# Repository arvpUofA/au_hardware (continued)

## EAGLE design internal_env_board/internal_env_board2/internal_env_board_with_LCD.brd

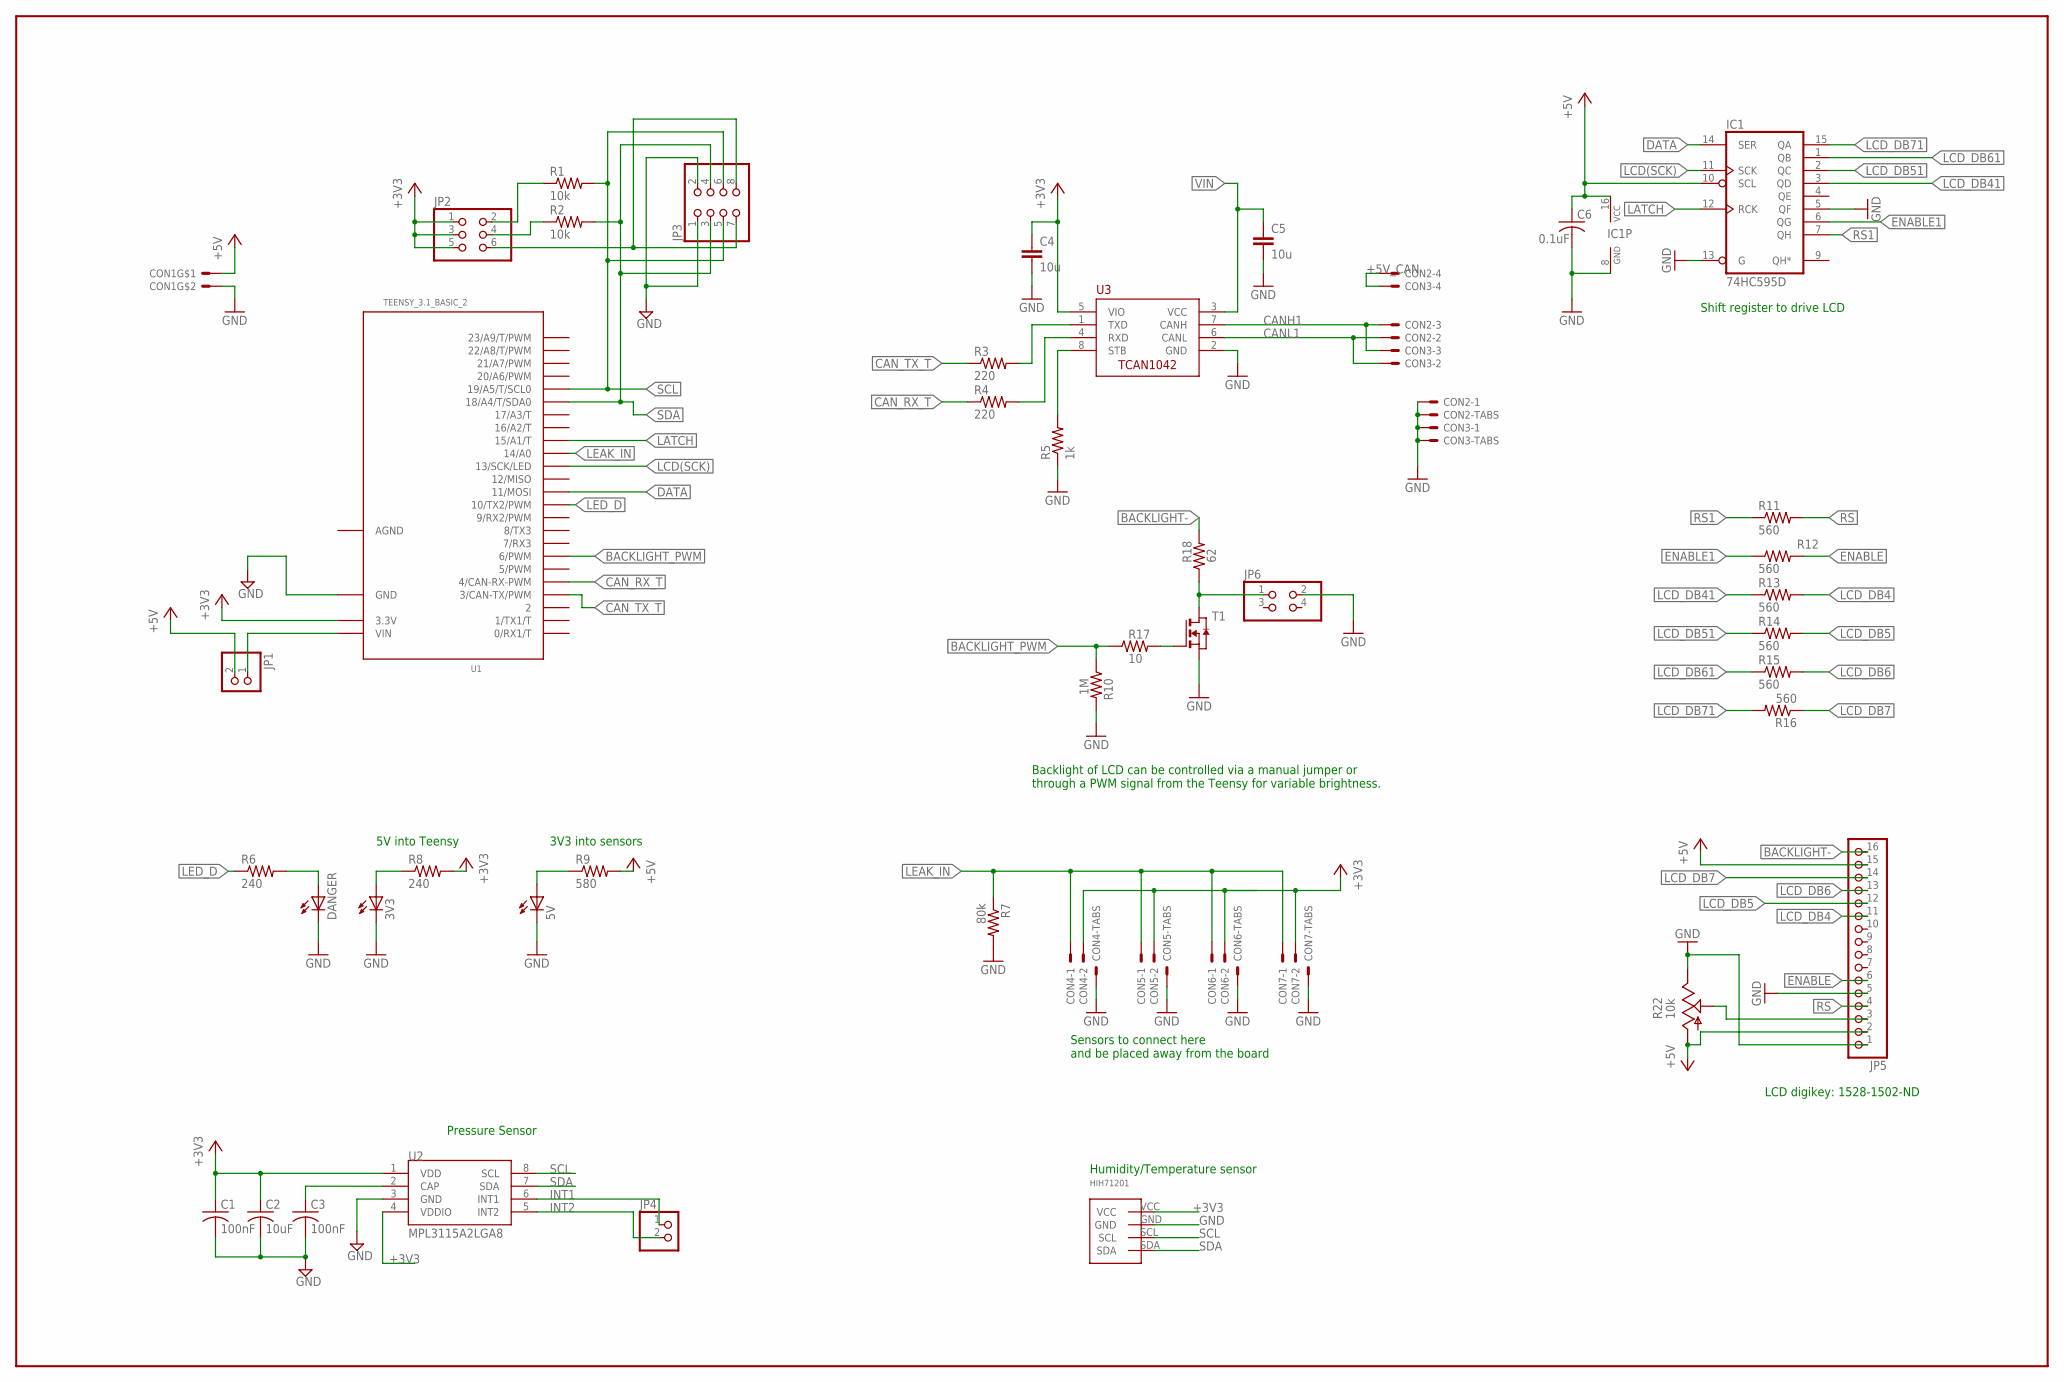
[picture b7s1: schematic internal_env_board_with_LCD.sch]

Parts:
3V3, 5V: LEDSMT1206; 1206
C1, C3: 100nF; C1206
C2: 10uF; C1206
C4, C5: 10u; C0805
C6: 0.1uF; C2012
CON1: MOLEX_5566-2; 5566-2
CON2, CON3: SM04B-GHS-TB
CON4, CON5, CON6, CON7: SM02B-GHS-TB
DANGER: LEDSMT1206; 1206
HIH71201: HIH7120; SIP4
IC1: 74HC595D; SO16
JP1, JP4: PINHD-1X2; 1X02
JP2: PINHD-2X3; 2X03
JP3: PINHD-2X4; 2X04
JP5: PINHD-1X16; 1X16
JP6: PINHD-2X2; 2X02
R1, R2: 10k; R1206
R3, R4: 220; R0805
R5: 1k; R0805
R6, R8: 240; R1206
R7: 80k; R1206
R9: 580; R1206
R10: 1M; R0805
R11, R12, R13, R14, R15, R16: 560; M2012
R17: 10; R0805
R18: 62; R0805
R22: 10k; SM-42/43W
T1: NMOSSOT23; SOT-23
U1: TEENSY_3.1_BASIC_2
U2: MPL3115A2LGA8; LGA8
U3: TCAN1042HVDR; SO-8

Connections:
+3V3: C1.1, C2.1, C4.1, CON4.P$2, CON5.P$2, CON6.P$2, CON7.P$2, HIH71201.VCC, JP2.1, JP2.3, JP2.5, R8.2, U1.3.3V, U2.1 (VDD), U2.4 (VDDIO), U3.5 (VIO)
+5V: C6.1, CON1.1, IC1.10 (SCL), IC1.16 (VCC), JP1.2, JP5.2, JP5.15, R9.2, R22.1 (A)
+5V_CAN: CON2.P$4, CON3.P$4
AGND: U1.AGND
BACKLIGHT-: JP5.16, R18.2
BACKLIGHT_PWM: R10.1, R17.1, U1.6 (6/PWM)
CANH1: CON2.P$3, CON3.P$3, U3.7 (CANH)
CANL1: CON2.P$2, CON3.P$2, U3.6 (CANL)
CAN_RX1: R4.2, U3.4 (RXD)
CAN_RX_T: R4.1, U1.4 (4/CAN-RX-PWM)
CAN_TX2: R3.2, U3.1 (TXD)
CAN_TX_T: R3.1, U1.3 (3/CAN-TX/PWM)
CAP: C3.1, U2.2 (CAP)
DATA: IC1.14 (SER), U1.11 (11/MOSI)
ENABLE: JP5.6, R12.2
ENABLE1: IC1.6 (QG), R12.1
GND: 3V3.C, 5V.C, C1.2, C2.2, C3.2, C4.2, C5.2, C6.2, CON1.2, CON2.P$1, CON2.P$5, CON2.P$6, CON3.P$1, CON3.P$5, CON3.P$6, CON4.P$3, CON4.P$4, CON5.P$3, CON5.P$4, CON6.P$3, CON6.P$4, CON7.P$3, CON7.P$4, DANGER.C, HIH71201.GND, IC1.5 (QF), IC1.8 (GND), IC1.13 (G), JP3.1, JP3.2, JP5.1, JP5.5, JP6.2, R5.1, R7.2, R10.2, R22.3 (E), T1.2 (S), U1.GND, U2.3 (GND), U3.2 (GND)
I2C_3V1: JP2.6, JP3.7, JP3.8
INT1: JP4.1, U2.6 (INT1)
INT2: JP4.2, U2.5 (INT2)
LATCH: IC1.12 (RCK), U1.15/A1 (15/A1/T)
LCD(SCK): IC1.11 (SCK), U1.13 (13/SCK/LED)
LCD_DB4: JP5.11, R13.2
LCD_DB5: JP5.12, R14.2
LCD_DB6: JP5.13, R15.2
LCD_DB7: JP5.14, R16.1
LCD_DB41: IC1.3 (QD), R13.1
LCD_DB51: IC1.2 (QC), R14.1
LCD_DB61: IC1.1 (QB), R15.1
LCD_DB71: IC1.15 (QA), R16.2
LEAK_IN: CON4.P$1, CON5.P$1, CON6.P$1, CON7.P$1, R7.1, U1.14/A0
LED_D: R6.1, U1.10 (10/TX2/PWM)
unnamed: DANGER.A, R6.2
unnamed: 5V.A, R9.1
unnamed: R17.2, T1.3 (G)
unnamed: JP6.1, R18.1, T1.1 (D)
unnamed: 3V3.A, R8.1
unnamed: JP5.3, R22.2 (S)
RS: JP5.4, R11.2
RS1: IC1.7 (QH), R11.1
SCL: HIH71201.SCL, JP3.5, JP3.6, R1.2, U1.19/A5 (19/A5/T/SCL0), U2.8 (SCL)
SCL_3V1: JP2.2, R1.1
SDA: HIH71201.SDA, JP3.3, JP3.4, R2.2, U1.18/A4 (18/A4/T/SDA0), U2.7 (SDA)
SDA_3V1: JP2.4, R2.1
STB1: R5.2, U3.8 (STB)
VIN: C5.1, JP1.1, U1.VIN, U3.3 (VCC)

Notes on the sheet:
Pressure Sensor
5V into Teensy
3V3 into sensors
Humidity/Temperature sensor
Sensors to connect here and be placed away from the board
LCD digikey: 1528-1502-ND
Shift register to drive LCD
Backlight of LCD can be controlled via a manual jumper or through a PWM signal from the Teensy for variable brightness.

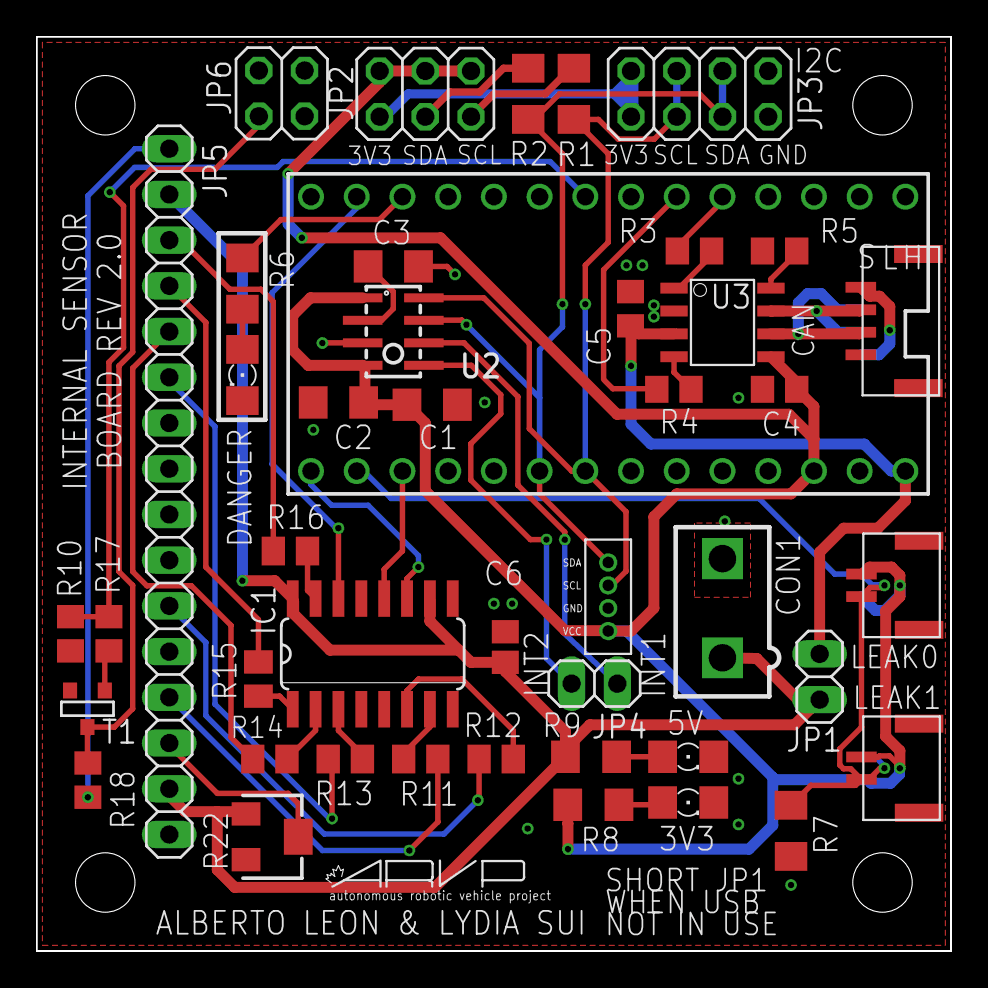
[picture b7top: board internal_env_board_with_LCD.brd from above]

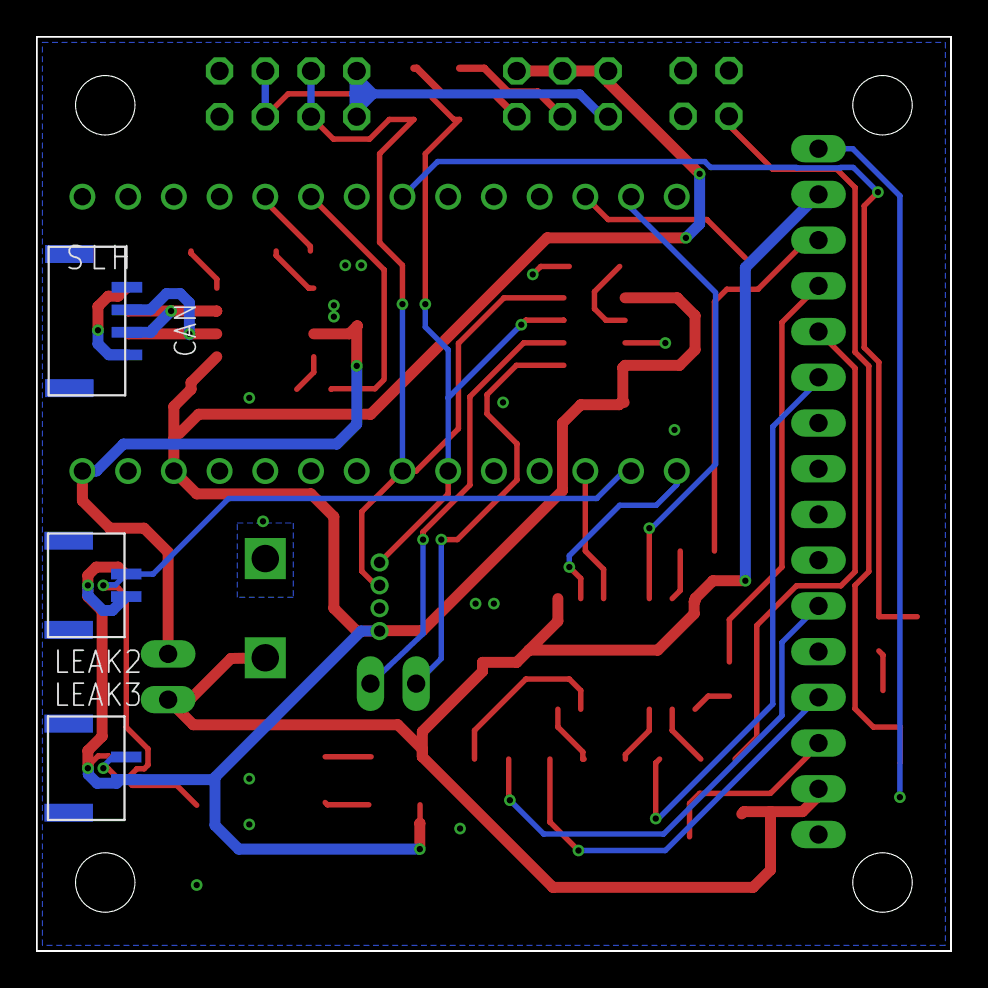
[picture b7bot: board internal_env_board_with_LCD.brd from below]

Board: 2 copper layers, 50.8 x 50.8 mm, 53 parts (3 on the bottom side), 45 nets.

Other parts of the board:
U$1: LOGO2
U$4: A5L-LOC
U$5, U$6, U$7, U$8: STAND-OFF

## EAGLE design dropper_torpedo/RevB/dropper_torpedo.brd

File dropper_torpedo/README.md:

<p>This is the dropper torpedo board schematic</p>
<p>Board layout will be added soon</p>

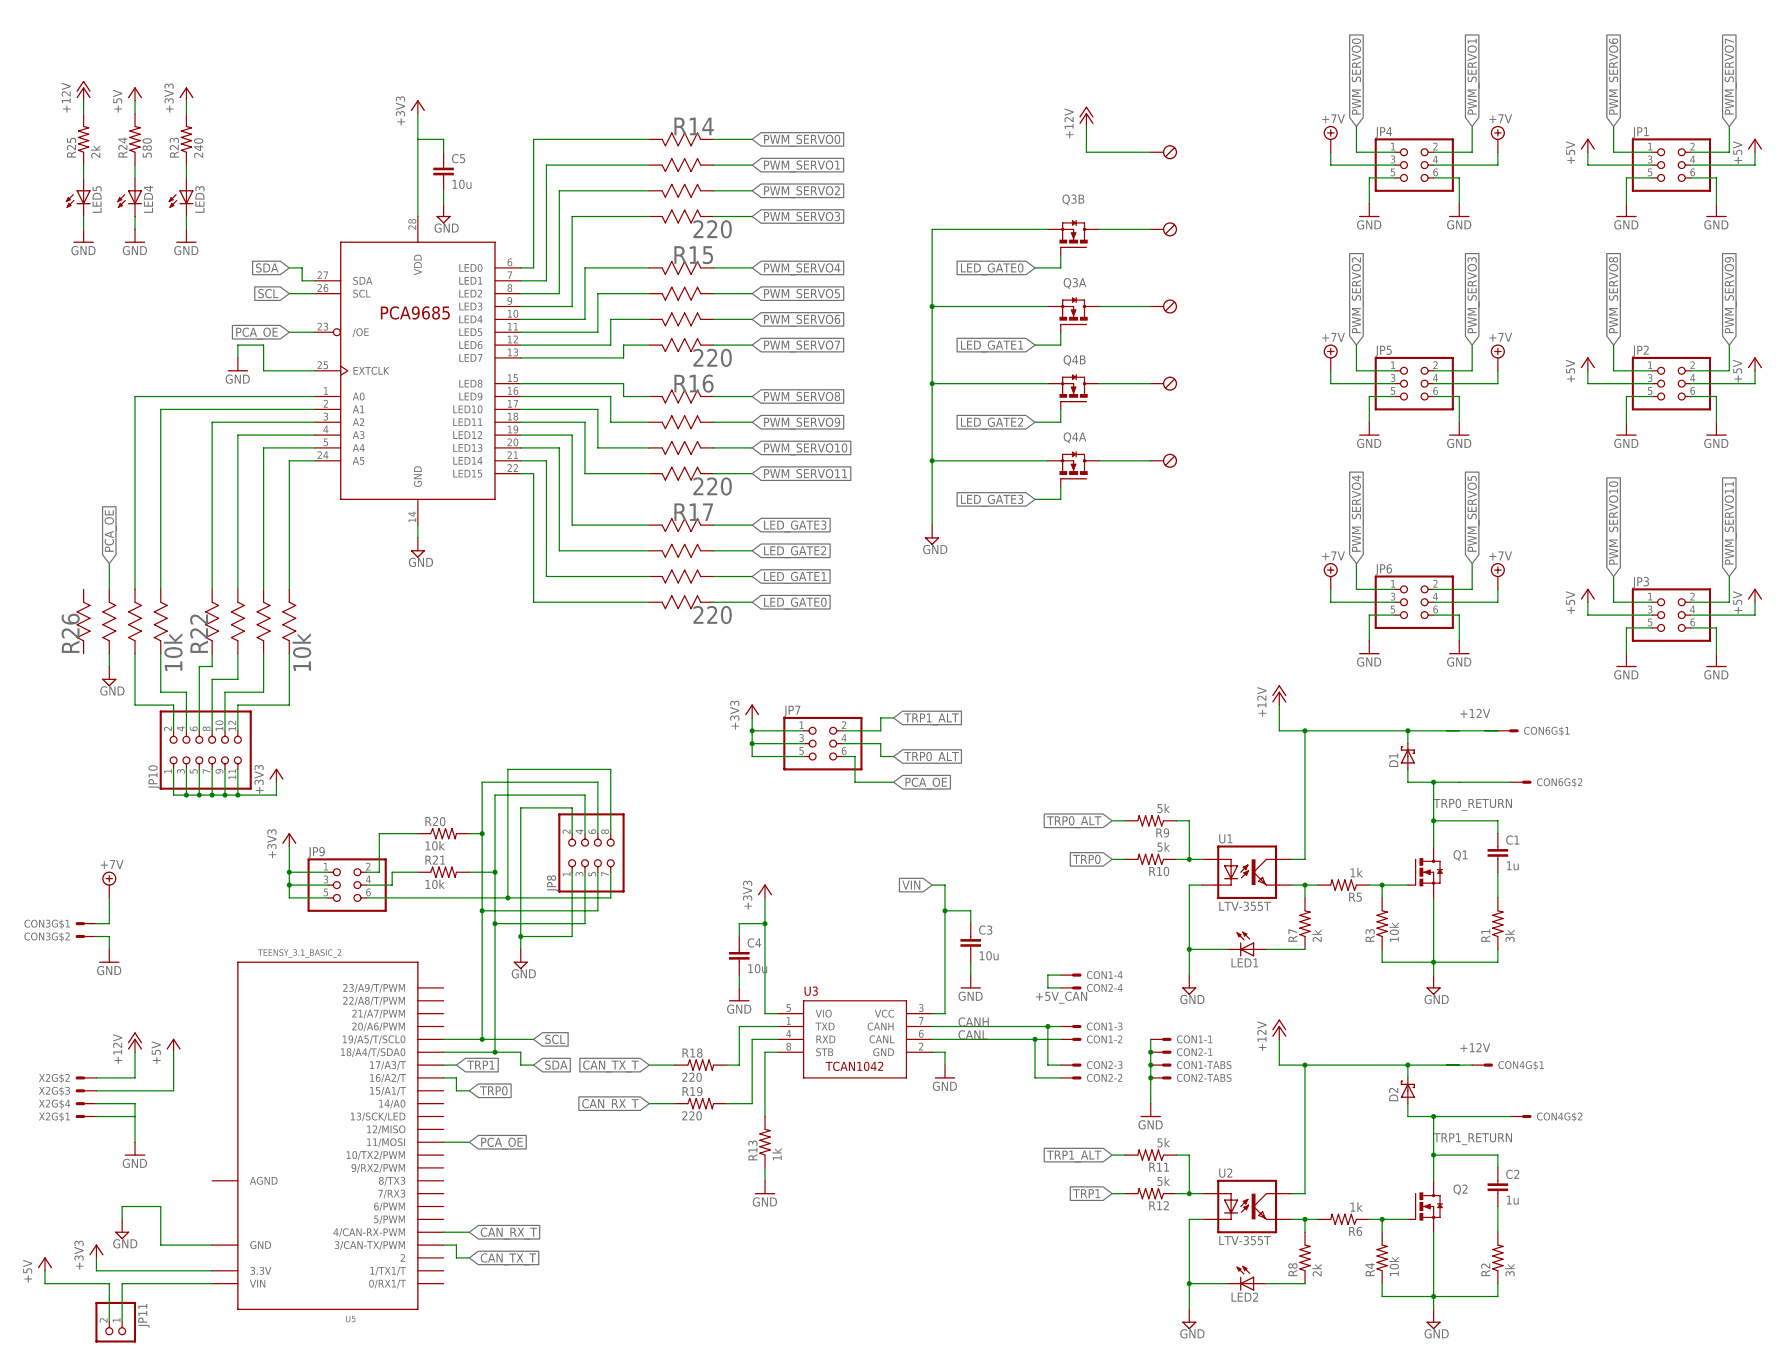
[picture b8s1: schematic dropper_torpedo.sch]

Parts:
C1, C2: 1u; C1206
C3, C4, C5: 10u; C0805
CON1, CON2: SM04B-GHS-TB
CON3, CON4, CON6: MOLEX_5566-2; 5566-2
D1, D2: STPS1L30A; DO214AC
JP1, JP2, JP3, JP4, JP5, JP6, JP7, JP9: PINHD-2X3; 2X03
JP8: PINHD-2X4; 2X04
JP10: PINHD-2X6; 2X06
JP11: PINHD-1X2; 1X02
LED1, LED2, LED3, LED4, LED5: LEDCHIPLED_1206; CHIPLED_1206
Q1, Q2: SI4896DY-T1-E3; SO-8
Q3, Q4: IRL6372TRPBF; SO-8
R1, R2: 3k; R1206
R3, R4, R20, R21: 10k; R1206
R5, R6: 1k; R1206
R7, R8, R25: 2k; R1206
R9, R10, R11, R12: 5k; R0805
R13: 1k; R0805
R14, R15, R16, R17: 220; EXBV8V-M
R18, R19: 220; R0805
R22, R26: 10k; EXBV8V-M
R23: 240; R1206
R24: 580; R1206
U1, U2: LTV-355T; SMD4
U3: TCAN1042HVDR; SO-8
U4: PCA9685PW; TSSOP28
U5: TEENSY_3.1_BASIC_2
X1: OSTVN05A150
X2: MOLEX_5566-4; 5566-4

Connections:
+3V3: C4.1, C5.1, JP7.1, JP7.3, JP7.5, JP9.1, JP9.3, JP9.5, JP10.1, JP10.3, JP10.5, JP10.7, JP10.9, JP10.11, R23.2, U3.5 (VIO), U4.28 (VDD), U5.3.3V
+5V: JP1.3, JP1.4, JP2.3, JP2.4, JP3.3, JP3.4, JP11.2, R24.2, X2.3
+5V_CAN: CON1.P$4, CON2.P$4
+7V: CON3.1, JP4.3, JP4.4, JP5.3, JP5.4, JP6.3, JP6.4
+12V: CON4.1, CON6.1, D1.C, D2.C, R25.2, U1.COLLECTOR (COL), U2.COLLECTOR (COL), X1.P$5, X2.2
A0: R26.6 (66), U4.1 (A0)
A0+: JP10.2, R26.3 (35)
A1: R26.5 (58), U4.2 (A1)
A1+: JP10.4, R26.4 (47)
A2: R22.8 (82), U4.3 (A2)
A2+: JP10.6, R22.1 (11)
A3: R22.7 (74), U4.4 (A3)
A3+: JP10.8, R22.2 (23)
A4: R22.6 (66), U4.5 (A4)
A4+: JP10.10, R22.3 (35)
A5: R22.5 (58), U4.24 (A5)
A5+: JP10.12, R22.4 (47)
AGND: U5.AGND
CANH: CON1.P$3, CON2.P$3, U3.7 (CANH)
CANL: CON1.P$2, CON2.P$2, U3.6 (CANL)
CAN_RX: R19.2, U3.4 (RXD)
CAN_RX_T: R19.1, U5.4 (4/CAN-RX-PWM)
CAN_TX1: R18.2, U3.1 (TXD)
CAN_TX_T: R18.1, U5.3 (3/CAN-TX/PWM)
GND: C3.2, C4.2, C5.2, CON1.P$1, CON1.P$5, CON1.P$6, CON2.P$1, CON2.P$5, CON2.P$6, CON3.2, JP1.5, JP1.6, JP2.5, JP2.6, JP3.5, JP3.6, JP4.5, JP4.6, JP5.5, JP5.6, JP6.5, JP6.6, JP8.1, JP8.2, LED1.C, LED2.C, LED3.C, LED4.C, LED5.C, Q1.1 (S), Q1.2 (S), Q1.3 (S), Q2.1 (S), Q2.2 (S), Q2.3 (S), Q3.1 (S), Q3.3 (S), Q4.1 (S), Q4.3 (S), R1.1, R2.1, R3.1, R4.1, R13.1, R26.2 (23), U1.CATHODE (C), U2.CATHODE (C), U3.2 (GND), U4.14 (GND), U4.25 (EXTCLK), U5.GND, X2.1, X2.4
I2C_3V3: JP8.7, JP8.8, JP9.6
LED_DRAIN0: Q3.7 (D), Q3.8 (D), X1.P$4
LED_DRAIN1: Q3.5 (D), Q3.6 (D), X1.P$3
LED_DRAIN2: Q4.7 (D), Q4.8 (D), X1.P$2
LED_DRAIN3: Q4.5 (D), Q4.6 (D), X1.P$1
LED_GATE0: Q3.2 (G), R17.4 (47)
LED_GATE1: Q3.4 (G), R17.3 (35)
LED_GATE2: Q4.2 (G), R17.2 (23)
LED_GATE3: Q4.4 (G), R17.1 (11)
unnamed: LED1.A, R7.1
unnamed: LED2.A, R8.1
unnamed: LED3.A, R23.1
unnamed: LED4.A, R24.1
unnamed: LED5.A, R25.1
PCA_OE: JP7.6, R26.7 (74), U4.23 (/OE), U5.11 (11/MOSI)
PWM_CH0: R14.8 (82), U4.6 (LED0)
PWM_CH1: R14.7 (74), U4.7 (LED1)
PWM_CH2: R14.6 (66), U4.8 (LED2)
PWM_CH3: R14.5 (58), U4.9 (LED3)
PWM_CH4: R15.8 (82), U4.10 (LED4)
PWM_CH5: R15.7 (74), U4.11 (LED5)
PWM_CH6: R15.6 (66), U4.12 (LED6)
PWM_CH7: R15.5 (58), U4.13 (LED7)
PWM_CH8: R16.8 (82), U4.15 (LED8)
PWM_CH9: R16.7 (74), U4.16 (LED9)
PWM_CH10: R16.6 (66), U4.17 (LED10)
PWM_CH11: R16.5 (58), U4.18 (LED11)
PWM_CH12: R17.8 (82), U4.19 (LED12)
PWM_CH13: R17.7 (74), U4.20 (LED13)
PWM_CH14: R17.6 (66), U4.21 (LED14)
PWM_CH15: R17.5 (58), U4.22 (LED15)
PWM_SERVO0: JP4.1, R14.1 (11)
PWM_SERVO1: JP4.2, R14.2 (23)
PWM_SERVO2: JP5.1, R14.3 (35)
PWM_SERVO3: JP5.2, R14.4 (47)
PWM_SERVO4: JP6.1, R15.1 (11)
PWM_SERVO5: JP6.2, R15.2 (23)
PWM_SERVO6: JP1.1, R15.3 (35)
PWM_SERVO7: JP1.2, R15.4 (47)
PWM_SERVO8: JP2.1, R16.1 (11)
PWM_SERVO9: JP2.2, R16.2 (23)
PWM_SERVO10: JP3.1, R16.3 (35)
PWM_SERVO11: JP3.2, R16.4 (47)
RC0: C1.2, R1.2
RC1: C2.2, R2.2
SCL: JP8.5, JP8.6, R20.2, U4.26 (SCL), U5.19/A5 (19/A5/T/SCL0)
SCL_3V3: JP9.2, R20.1
SDA: JP8.3, JP8.4, R21.2, U4.27 (SDA), U5.18/A4 (18/A4/T/SDA0)
SDA_3V3: JP9.4, R21.1
STB: R13.2, U3.8 (STB)
TOPTO_A0: R9.1, R10.1, U1.ANODE (A)
TOPTO_A1: R11.1, R12.1, U2.ANODE (A)
TOPTO_E0: R5.2, R7.2, U1.EMITTER (EMIT)
TOPTO_E1: R6.2, R8.2, U2.EMITTER (EMIT)
TRP0: R10.2, U5.16/A2 (16/A2/T)
TRP0_ALT: JP7.4, R9.2
TRP0_RETURN: CON6.2
TRP1: R12.2, U5.17/A3 (17/A3/T)
TRP1_ALT: JP7.2, R11.2
TRP1_RETURN: C2.1, CON4.2, D2.A, Q2.5 (D), Q2.6 (D), Q2.7 (D), Q2.8 (D)
TRP_GATE0: Q1.4 (G), R3.2, R5.1
TRP_GATE1: Q2.4 (G), R4.2, R6.1
TRP_RETURN0: C1.1, D1.A, Q1.5 (D), Q1.6 (D), Q1.7 (D), Q1.8 (D)
VIN: C3.1, JP11.1, U3.3 (VCC), U5.VIN

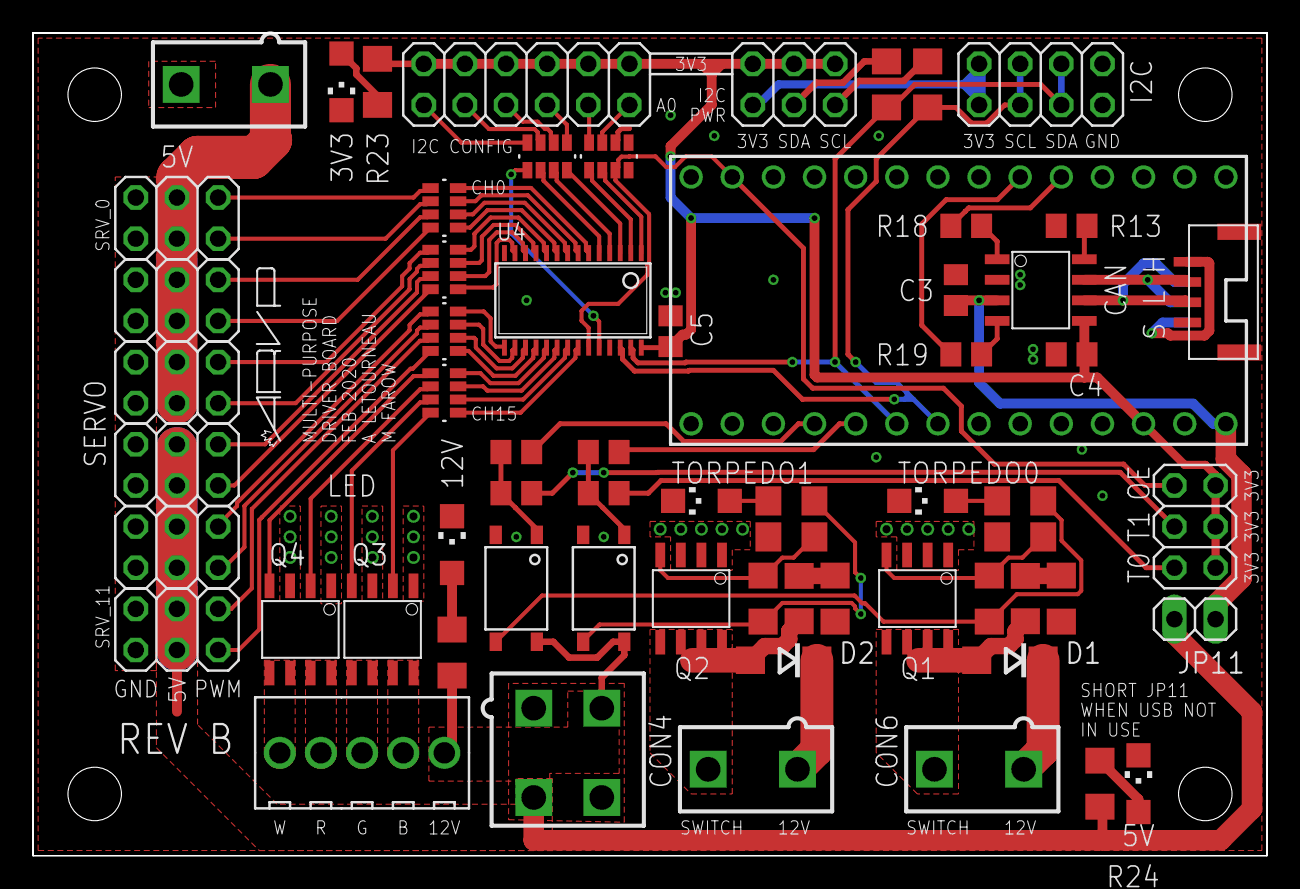
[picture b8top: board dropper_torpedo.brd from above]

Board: 2 copper layers, 76.2 x 50.8 mm, 72 parts (1 on the bottom side), 87 nets.

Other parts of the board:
U$5: LOGO3
U$6: LETTER_L
U$7: DOCFIELD
U$8, U$9, U$10, U$11: STAND-OFF

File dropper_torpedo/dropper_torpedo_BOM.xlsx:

Torpedo Board V3: Bill of Materials
Shematic Reference Number | Part Description | Manufacturer Part Number | Datasheet | Price | Quantity | Total Cost | Customer Reference
Q1, Q2 | MOSFET N-CH 80V 6.7A 8-SOIC | SI4896DY-T1-E3 | http://www.vishay.com/docs/71300/71300.pdf | 2.37 | 2 | 4.74 | DROP_TORP
Q3, Q4 | MOSFET 2N-CH 30V 8.1A 8SOIC | IRL6372TRPBF | http://www.infineon.com/dgdl/irl6372pbf.pdf?fileId=5546d4625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 | 1.15 | 2 | 2.3 | DROP_TORP
D1, D2 | DIODE SCHOTTKY 30V 1A SMA | STPS1L30A | http://www.st.com/content/ccc/resource/technical/document/da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 | 0.53 | 2 | 1.06 | DROP_TORP
U1, U2 | OPTOISO 3.75KV DARLINGTON 4SOP | LTV-355T | http://optoelectronics.liteon.com/upload/download/DS70-2001-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 | 0.74 | 2 | 1.48 | DROP_TORP
TRM1, TRM2 | TERM BLOCK 5.08MM HORZ 2POS PCB | OSTTC022162 | http://www.on-shore.com/wp-content/uploads/2015/09/osttcxx2162.pdf | 1.08 | 2 | 2.16 | DROP_TORP
LED1-5 | LED GREEN CLEAR 1206 SMD | LTST-C150GKT | http://optoelectronics.liteon.com/upload/download/DS-22-98-0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 | 0.46 | 2 | 0.92 | DROP_TORP
X2 | CONN HEADER 4POS 4.2MM VERT TIN | 39281043 | http://www.molex.com/pdm_docs/sd/039281043_sd.pdf | 1.04 | 1 | 1.04 | DROP_TORP
R14-17 | RES ARRAY 4 RES 220 OHM 1206 | EXB-V8V221JV | https://media.digikey.com/pdf/Data%20Sheets/Panasonic%20Resi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 | 0.14 | 4 | 0.56 | DROP_TORP
R22,26 | RES ARRAY 4 RES 10K OHM 1206 | EXB-V8V103JV | https://media.digikey.com/pdf/Data%20Sheets/Panasonic%20Resi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 | 0.14 | 2 | 0.28 | DROP_TORP
X1 | CONN TERM BLOCK 2.54MM 5POS PCB | OSTVN05A150 | http://www.on-shore.com/wp-content/uploads/2015/09/ostvnxxa150.pdf | 2.34 | 1 | 2.34 | DROP_TORP
C1,2 | CAP CER 1UF 50V X7R 1206 | CL31B105KBHNNNE | https://www.samsungsem.com/kr/support/product-search/mlcc/__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 | 0.26 | 2 | 0.52 | DROP_TORP
C3,4,5 | CAP CER 10UF 16V X7R 0805 | CL21B106KOQNNNG | http://www.samsungsem.com/kr/support/product-search/mlcc/CL2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 | 0.39 | 3 | 1.17 | DROP_TORP
R23 | RES SMD 240 OHM 1% 1/4W 1206 | RC1206FR-07240RL | http://www.yageo.com/documents/recent/PYu-RC_Group_51_RoHS_L_7.pdf | 0.047 | 1 | 0.047 | DROP_TORP
R24 | RES SMD 576 OHM 1% 1/4W 1206 | RC1206FR-07576RL | http://www.yageo.com/documents/recent/PYu-RC_Group_51_RoHS_L_7.pdf | 0.047 | 1 | 0.047 | DROP_TORP
R5,6 | RES SMD 1K OHM 1% 1/4W 1206 | RC1206FR-071KL | http://www.yageo.com/documents/recent/PYu-RC_Group_51_RoHS_L_7.pdf | 0.047 | 2 | 0.094 | DROP_TORP
R7,8,25 | RES SMD 2K OHM 1% 1/4W 1206 | RC1206FR-072KL | http://www.yageo.com/documents/recent/PYu-RC_Group_51_RoHS_L_7.pdf | 0.047 | 3 | 0.141 | DROP_TORP
R9-12 | RES SMD 4.99K OHM 1% 1/4W 0805 | RC0805FR-074K99L | http://www.yageo.com/documents/recent/PYu-RC_Group_51_RoHS_L_8.pdf | 0.031 | 4 | 0.124 | DROP_TORP
R18, 19 | RES SMD 220 OHM 1% 1/8W 0805 | RC0805FR-07220RL | http://www.yageo.com/documents/recent/PYu-RC_Group_51_RoHS_L_7.pdf | 0.031 | 2 | 0.062 | DROP_TORP
R1,2 | RES SMD 3K OHM 1% 1/4W 1206 | RC1206FR-073KL | http://www.yageo.com/documents/recent/PYu-RC_Group_51_RoHS_L_7.pdf | 0.047 | 2 | 0.094 | DROP_TORP
R3,4,20,21 | RES SMD 10K OHM 1% 1/4W 1206 | RC1206FR-0710KL | http://www.yageo.com/documents/recent/PYu-RC_Group_51_RoHS_L_7.pdf | 0.047 | 4 | 0.188 | DROP_TORP
R13 | RES SMD 1K OHM 1% 1/8W 0805 | RC0805FR-071KL | http://www.yageo.com/documents/recent/PYu-RC_Group_51_RoHS_L_7.pdf | 0.034 | 1 | 0.034 | DROP_TORP
U4 | IC LED DRIVER RGBA 28-TSSOP | PCA9685PW,118 | http://www.nxp.com/documents/data_sheet/PCA9685.pdf | 3.3 | 1 | 3.3 | DROP_TORP
Teensy 3.2 | CONN HEADER FMALE 14POS .1" GOLD | PPPC141LFBN-RC | http://www.sullinscorp.com/drawings/78_P(N)PxCxxxLFBN-RC,_10492-H.pdf | 1.28 | 2 | 2.56 | DROP_TORP
JP1-7,9,10 | DIL VERTICAL PC TAIL PIN HEADER 2x3 | M20-9980345 | https://cdn.harwin.com/pdfs/M20-998.pdf | 0.348 | 9 | 3.132 | DROP_TORP
JP8 | DIL VERTICAL PC TAIL PIN HEADER 2x4 | M20-9980445 | https://cdn.harwin.com/pdfs/M20-998.pdf | 0.48 | 1 | 0.48 | DROP_TORP
JP11 | SIL VERTICAL PC TAIL PIN HEADER 1x2 | M20-9990245 | https://cdn.harwin.com/pdfs/M20-999.pdf | 0.2 | 1 | 0.2 | DROP_TORP
U3 | IC TXRX CAN FAULT PROT 8SOIC | TCAN1042HVDRQ1 | http://www.ti.com/lit/ds/symlink/tcan1042hgv-q1.pdf | 2.05 | 1 | 2.05 | DROP_TORP
CON3 | CONN HEADER 2POS 4.2MM VERT TIN | 39281023 | http://www.molex.com/pdm_docs/sd/039281023_sd.pdf | 0.83 | 1 | 0.83 | DROP_TORP
CON1,2 | CONN HEADER GH SIDE 3POS 1.25MM | SM03B-GHS-TB(LF)(SN) | http://www.jst-mfg.com/product/pdf/eng/eGH.pdf | 0.68 | 2 | 1.36 | DROP_TORP
- | CONN JUMPER SHORTING GOLD FLASH | SPC02SYAN | http://www.sullinscorp.com/drawings/134_C02SYAN_11134.pdf | 0.083 | 9 | 0.747 | DROP_TORP
 |  |  |  |  | Total | 34.06

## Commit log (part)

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2017-11-07 Fixed issue with CAM files
2017-11-11 Schematic
2017-11-13 Schematic with suggestions made by Alain implemented.
    I've implemented the suggestions from the last meeting, and I will begin work on the PCB once it is reviewed.
2017-11-14 not sure how to add the yellow signal lines
2017-11-14 implemented newest design block and rearranged pcb
2017-11-17 Schematic: Update with MOSFET to switch PV_OUT
2017-11-18 2x2 inch board and trace routes
2017-11-20 Updated CAN Design Block To use JST connectors.
2017-11-22 changed dimensions and fixed layer text
2017-11-23 Schematic with name changes on the LEDs
2017-11-24 Schematic: Value of a resistor is changed
2017-11-25 Swapped old MPL3115 footprint with new one
2017-11-25 In BOM, changed .47uF capacitor to one with .55mm thickness
2017-11-25 Schematic: Connected pin 3 on JP2 to VCC
2017-11-25 Board (v.4)
    Fixed the issue of islanding.
2017-11-25 Added jumpers to schematic and finished the PCB. The PCB has not been checked with the new DRC.
2017-11-26 schematic for i2c,uart, LEDs
2017-11-26 Rearranged file structure
2017-11-26 Removed extra folder
2017-11-28 CAM files, Image files
2017-11-29 Fixes as asked for in pull request
2017-11-30 Added jumpers for the shield connection on the JST connectors.
2017-11-30 Added jumpers for CAN enable.
2017-12-01 Added jumpers to I2C
2017-12-01 minor fixes, cant find jst-gh part
2017-12-01 new conn for can bus and leak sensors, new routes
2017-12-02 Added some GND VIAs
2017-12-02 JST connectors, traces
2017-12-02 Spaced out JST connectors
2017-12-02 Completed schematic
2017-12-03 Slightly modified layout+routing
2017-12-03 Routed most components
2017-12-03 Changed folder structure
2017-12-03 Changed layout, routing; Generated CAM files
2017-12-03 Re-added old sch and brd
2017-12-03 Fixed issue where motors could still find ground return path even when battery was disconnected by mosfet
2017-12-03 Added 5V pin to CAN connectors in case ESC CAN transceivers require external 5V
2017-12-03 Increased text size for LEDs
2017-12-04 completed board
2017-12-04 Added BOM and the parts order list
2017-12-05 Added BOM; Changed LED resistor values
2017-12-05 Corrected 2x3 header qty in BOM
2017-12-06 Edited the BOM, cleaned up some errors.
2017-12-07 Fixed qty of 1x2 headers
2017-12-08 Fixed qty JST 2 pin conn
2017-12-08 Made BOM + CAM
2017-12-27 updated sonar part list with available qts
2018-01-14 Added libraries and design block
2018-01-17 Added LDO
2018-01-19 Schematic and board with fuse
2018-01-20 added power and communication wiring diagram. WIP
2018-01-22 Added proper paging and most power diagrams
2018-01-26 Board File Upload
2018-02-03 Final board design with png files for board and schematic
2018-02-04 Added base schematic file
2018-02-04 Added amplifier.dbl
2018-02-04 Added peak_detector.dbl
2018-02-04 Added nxp_60.lbr
2018-02-04 First Revision
    First Revision of the variable gain amplifier for the sonar board. Designed for testing.
2018-02-04 Revert "Merge branch 'amplifier' into sonar_preprocessor_v3"
    This reverts commit 540102cfd5a4b1681464287940d3c6b068a53623, reversing
    changes made to de64d5886ef795e5a61c97630054a831d31d3a9c.
2018-02-05 re-upload after failed merge
2018-02-06 added all components except for connectors and test points
2018-02-07 adjuste filter C parameters
2018-02-07 Using 0.2" pitch headers
2018-02-09 added sugestions from Mike Bardwell to schematic
2018-02-09 *forgot to save on previous commit
2018-02-10 added names to clk/i2c pins
2018-02-11 Completed changes discussed in last design review and ran through DRC
2018-02-11 Renamed files
2018-02-11 Modified silk screen
2018-02-12 Pushed BOM file
2018-02-12 Changed layer of dimensions; Added CAM files
2018-02-13 Complted bom, made a couple package changes on schematic to conver them to 0805
2018-02-19 Created initial peak detector design block
2018-03-10 Made some changes recommended by Alain, still need to do more
2018-03-10 Finished implementing Alain's recommendations
2018-03-10 Added BeagleBone custom cape lbr
2018-03-10 Replaced beaglebone footprint with some pinheaders
2018-03-12 Work on headers
2018-03-17 Final commit for peak detector, 100% verified working.
2018-03-21 Reworked board dimensions and mounting
2018-03-24 added filter design block
2018-03-24 5, 3.3, and -5V design
2018-03-29 Added the design block
    All components on the top layer. Made footprint as small as possible.
    Area is less than 15.30 x 10.9 mm
2018-03-30 Cheaper Options
2018-03-30 Added a little bit more clearance
2018-03-31 placed bypass caps and Rclk on bottom of board. Renamed BOM.xlsx to BOM_prototype.xlsx
2018-03-31 LT1117 and LT1962 schematics, PCBs, and design blocks
2018-03-31 added polarity indicator to Clock Generator
2018-04-04 More layout work
2018-04-04 Rearranged files
2018-04-05 Placed power supply, peak detector, filter
2018-04-13 reworked filter and clock routing
2018-04-13 Added clock output. minor clock routing changes
2018-04-14 some more work
2018-04-15 Started BOM
2018-04-20 Completed BOM; Routed peak detector BJT base
2018-05-10 First draft of the schematic and PCB
2018-05-10 deleted older versions
2018-05-12 Changed routings
2018-05-26 Removed extra GND pads, increased drill size to 1.5mm'
2018-05-26 Added mountable buffer board
2018-05-26 Modified layout
2018-05-27 Implemented Mikes suggestions
2018-05-27 Added CAM files; Changed power trace layout; Renamed test pads
2018-05-28 Changed VS routing, updated BOM
2018-05-29 leak detector added
2018-09-15 Added TVS diodes. Needs some work.
    Passes most DRC but has a few airwires.
2018-09-15 Turns out those airwires aren't an issue.
2018-10-20 Created new internal_sens_board sche for rerouting
2018-11-10 Deleted unused internal sensor board file
2018-11-10 Initial commit, board and schematic
2018-11-10 Added new board and schematic file
2018-11-11 Added images of board and schematic
2018-11-11 Created new folder structure for version 4
2018-11-11 Updated board file with guard rings and right angle BNC connectors.
2018-11-17 Completed error-checking, generated CAM
2018-11-20 Added sim, reorganized
2018-11-24 Added BOM spreadsheet
2018-11-25 Changed font sizes on the silkscreen
2018-11-25 Revert "Merge branch 'develop' into communications_hub-tvs-david"
    This reverts commit ab89ead97715090ee32798ddfa3cee6332a63a0d, reversing
    changes made to a250170e917bb120169c4520e22500f14d1f000b.
2018-11-26 PCB is done except for DRC, BOM is done
2018-12-01 Regenerated CAM data and re-ran error-check
2018-12-09 Updated picture of board and BOM
2018-12-12 Reduced board size to 5.7 x 2.0 inches.
2018-12-12 Fixed some polygons
2018-12-20 Added a transistor to the LCD backlight so it can be controlled by the Teensy. Also added a jumper so it can be turned on manually. Updated the BOM.
2018-12-20 Updated picture of schematic
2018-12-21 Added GND test point loop for oscilliscope ground probe and updated CAM files and schematica png.
2018-12-22 Added new components for LCD on board
2018-12-22 Added a new NMOS based LCD backlight control circuit to the schematic and board and add simulation files from LTspice.
2018-12-22 Revert "Added new components for LCD"
    This reverts commit b3b33264bb3048065967870ae9c2541e4a61a1bf.
2018-12-22 Revert "Added new components for LCD on board"
    This reverts commit 525a6551a790c18222fb1f502ed1c1a08163eb89.
2018-12-22 Generated updated CAM files.
2018-12-26 Added filters and formatting to BOM
2018-12-26 Added drill files
2019-01-26 Fixed a typo
2019-02-09 Changed pin headers to smaller ones for lower insertion force.
2019-04-02 Started integrated sonar ADCR project.
    Made STM32F303 device
2019-04-08 Largely done schematic.
    Still to do:
    - Teensy-style connections
    - Analog connections
    - Remember what else I'm forgetting.
2019-04-13 Theoretically done schematic.
    Need to verify again later when I have a fresh brain.
2019-04-13 Schematic is probably done for real now.
2019-04-18 Theoretically finished integrated ADC system.
2019-04-21 I should really be studying for finals.
    Final tweaks to schematic.
    I can't find anything terrible about either the layout or the schematic,
    but I'm certain there's something wrong.
2019-04-27 Commit of compact_LTM4607_PCB converter design from Alain.
2019-05-02 Implemented fixes/changes.
    The issues were discussed on April 30, 2019
2019-05-11 Fixed silkscreen, added new pdf for the board
2019-05-11 Changed sonar_preprocessorV4 to sonar_preprocessorV3.
2019-05-11 Added Auri Electrical Overview.
2019-05-15 New cam/gerber files
2019-05-19 The board layout is partially done, however some ground pins are isolated, I will try work on it tmr.
2019-05-21 png files and CAM files are added.
2019-05-23 Extra traces are removed, gound plane is added. Default DRC is passed. Info of the board is added as well.
2019-05-26 Added a new customer reference column in the BOM to indicate which board the parts are for. Digikey will apply the board name to the parts package which makes sorting the parts easier once they have 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
2019-05-26 BOM is added.
2019-05-28 Added another column to BOM for customer reference to make sorting parts easier when we get them.
2019-05-28 Added board name column for sorting purposes later.
2019-05-28 Modified BOM format and added new column for board name to make sorting parts easier.
2019-06-10 Stop mask added to LTC4418, new CAM files generated
2019-09-21 Modified electrical overview
2019-09-21 Removed some old testing breakout boards
2019-09-21 Removed 2017 motor driver boards
2019-09-21 Removed old power regulation board.
2019-09-21 renamed electrical overview schematic
2019-09-21 Added README
2019-10-22 Removed extraneous env board BOM file
2019-12-26 Added Schematic and BOM file
2020-01-19 Added channel, changed CAN transceiver, used NMOS
2020-02-02 Added PCB board file for battery levelling board
2020-03-05 dropper_torpedo: Fix up small errors
    Cleaned out DRC errors and fixed a net naming issue causing a short.
    Also tweaked the silkscreen to add Mustafa's name and a revision number.
2020-03-05 dropper_torpedo: added CAM exports
2020-03-28 Intermidiate Work-Board Tracing to be done
2020-05-02 battery_monitoring_board: Fixed up a few mistakes
    - Swapped battery terminal blocks around
    - Changed polygon fill from hatch to solid
    - Cleaned up polygons on 5th battery to match others
    - Removed vestigial polygons on bottom layer
    - Routed a few missing connections
    - Added Mustafa's name
2020-05-10 completed routing
2020-05-16 battery_monitoring: updated BOM [work done by Mustafa]
2020-05-16 dropper_torpedo: added RevB that Mustafa worked on
2020-05-16 dropper_torpedo: swapped out 3 pin JST for standards-based 4-pin
2020-05-17 internal_env_board: moved from 3-pin CAN to 4-pin CAN
2020-05-17 battery_levelling: changed to 4-pin CAN
2020-05-17 Exporting various gerbers
2020-05-18 killswitch: removed extraneous components from BOM
2020-06-26 Created ultrasonic_audio_amplifier folder
2020-07-25 Added board file.
2020-08-01 Updated board layout for review
2020-08-05 Modified I2C connector
2020-12-26 Added VBUS sensing logic
2021-01-12 copying files
2021-01-12 moving files
2021-01-12 moving files for Battery_Monitoring V4
2021-02-11 Removed duplicate teensy
2021-03-20 started work on PCB layout
2021-04-08 adjusting the resistor, capacitor, and ic positions
2021-05-08 minor component location changes
2021-05-12 renamed boards and fixed errors
2021-06-05 Realigned Parts
2021-06-08 Finished layout
2021-06-12 Shifted some components around
2021-06-18 Further shifted components, rerouted wires, resized board.
2021-07-23 Fixing trace width.
2021-09-11 Minor adjustments to layout
2021-09-25 Component placement
2021-10-09 Update testing.py
    Testing group repo
2021-10-16 Deleted test file
2021-11-08 Fix Rbias trace
2021-11-08 added ethernet library
2021-11-08 added ethernet library and final board image
2021-11-08 All components in place, beginning final tracing
2022-06-22 Working on traces
2022-09-12 Finished tracing, ran DRC
2023-01-25 Added tcl script and source/constraint files
2023-01-31 Added top level vhdl
2023-05-10 Added comments to top level source file
